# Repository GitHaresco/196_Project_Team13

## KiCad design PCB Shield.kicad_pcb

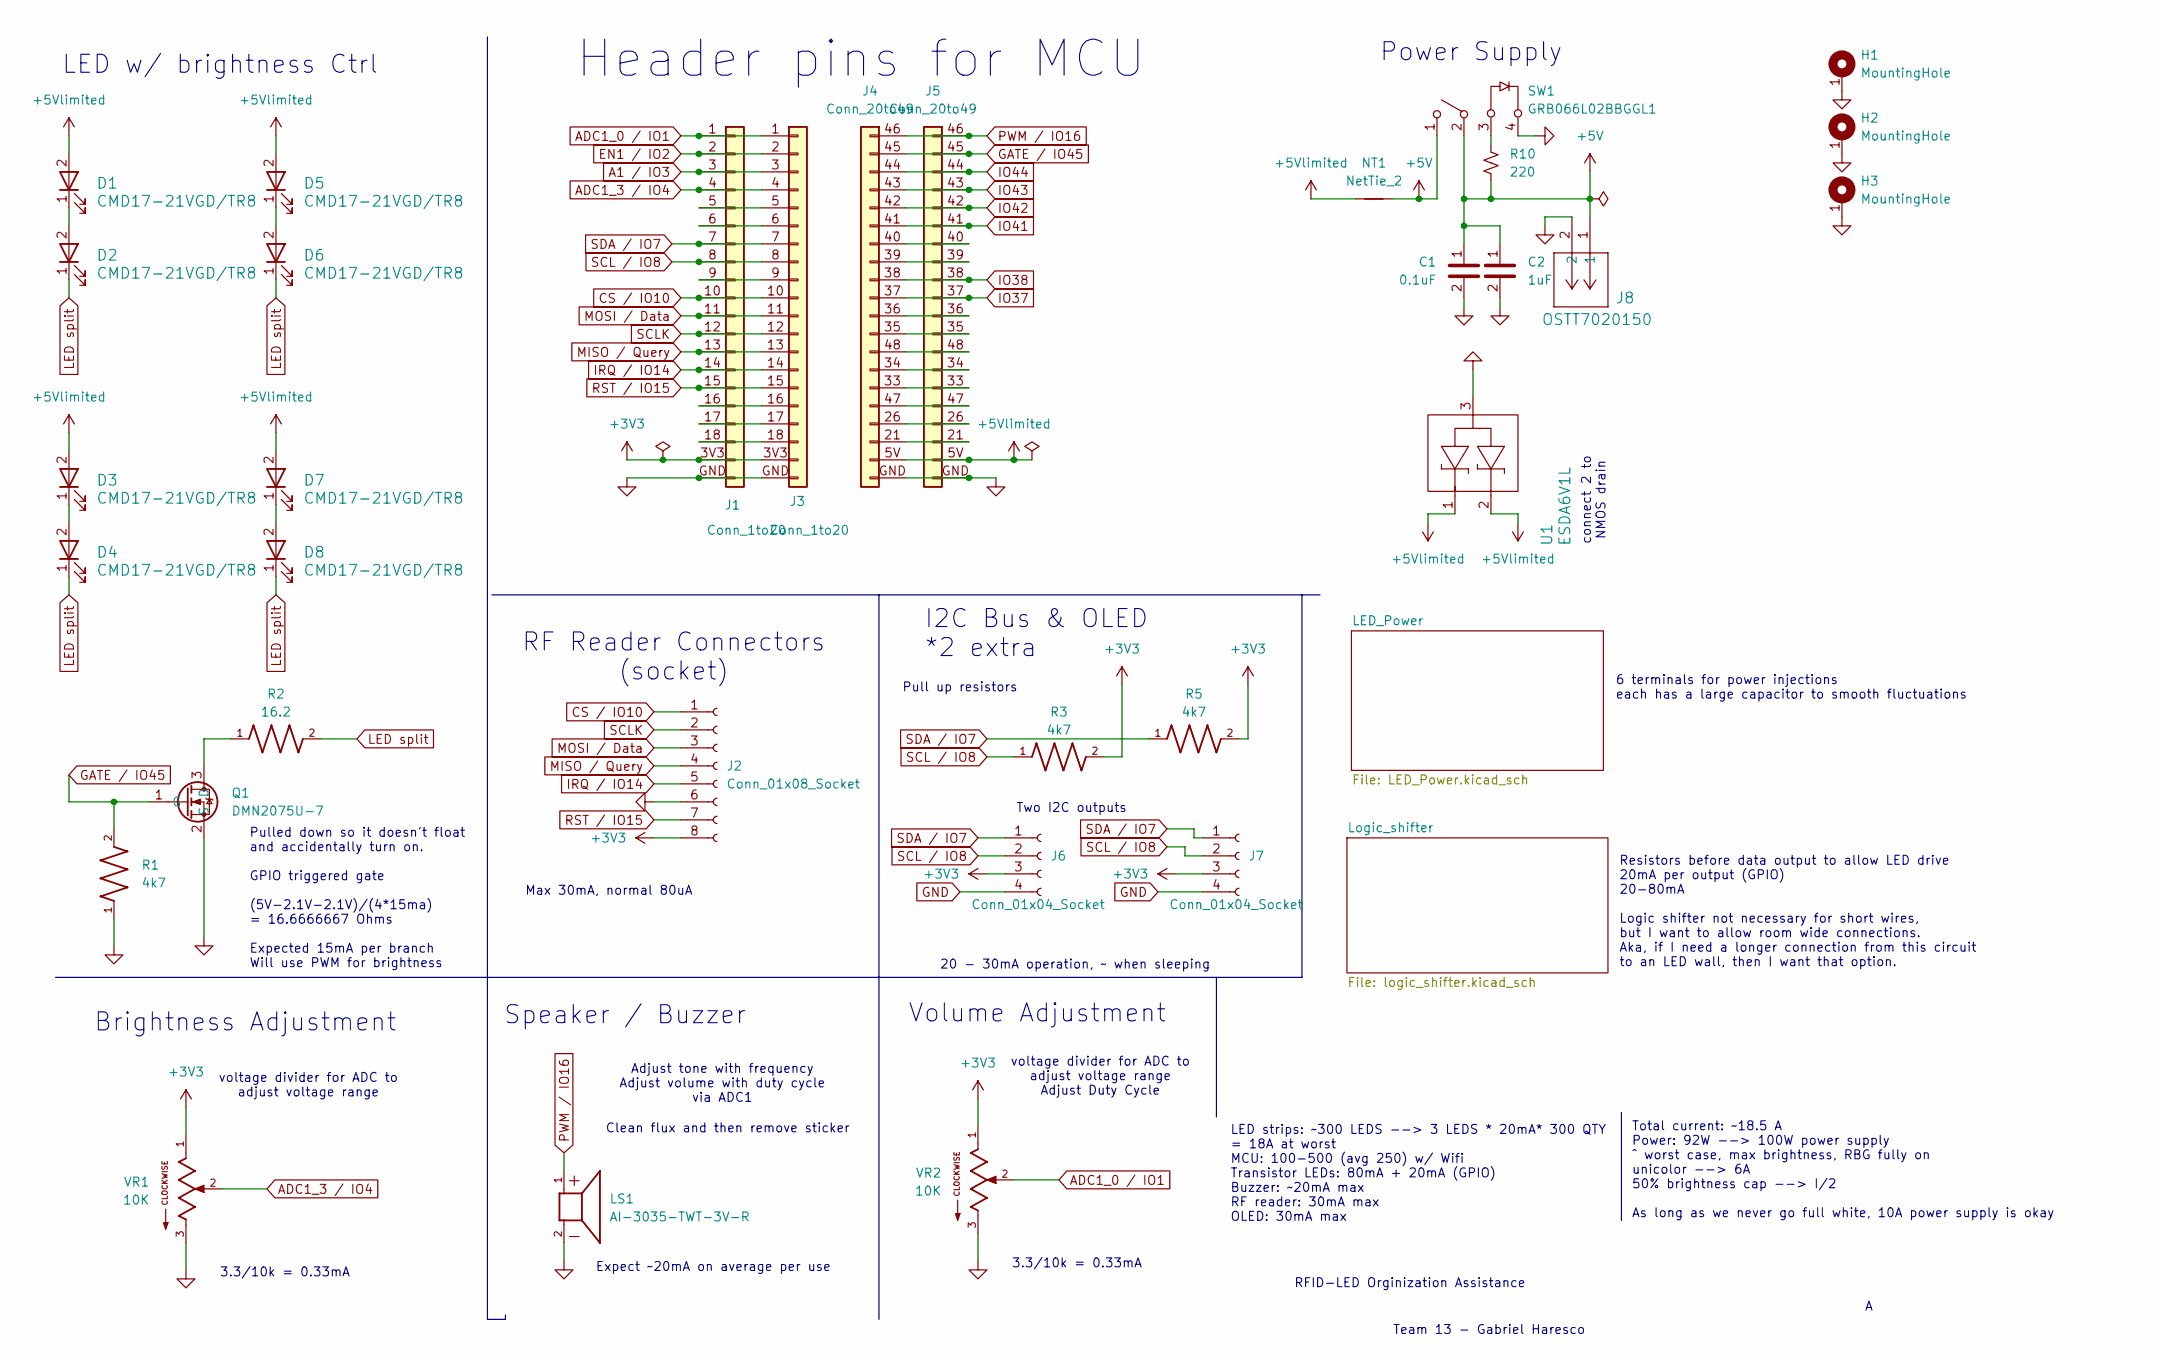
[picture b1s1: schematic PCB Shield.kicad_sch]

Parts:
C1: 0.1uF; CL31B104KBCNNNC; Part Number CL31B104KBCNNNC
C2: 1uF; CL31B105KAHNNNE; Part Number CL31B105KAHNNNE
D1, D2, D3, D4, D5, D6, D7, D8: CMD17-21VGD/TR8; CMD17-21VGD_TR8; Part Number CMD17-21VGD/TR8
H1, H2, H3: MountingHole
J1, J3: Conn_1to20; 196_Conn_1to20; Part Number PH1-20-UA
J2: Conn_01x08_Socket; PinSocket_1x08_P2.54mm_Vertical; Part Number PH1-20-UA
J4, J5: Conn_20to49; 196_Conn_20to48; Part Number PH1-20-UA
J6, J7: Conn_01x04_Socket; PinSocket_1x04_P2.54mm_Vertical; Part Number PH1-20-UA
J8: OSTT7020150; Part Number OSTT7020150
LS1: AI-3035-TWT-3V-R; Buzzer_12x9.5RM7.6; PARTREV E
NT1: NetTie_2; NetTie-2_SMD_Pad2.0mm
Q1: DMN2075U-7; SOT95P237X112-3N-2-V; Part Number DMN2075U-7
R1: 4k7; R_1206_3216Metric; Part Number CRCW120610K0FKEA
R2: 16.2; CRCW120616R2FKEA; Part Number CRCW120616R2FKEA
R3, R5: 4k7; RC1206FR-074K7L; Part Number RC1206FR-074K7L
R10: 220; R_1206_3216Metric; Part Number RCS1206150RJNEA
SW1: GRB066L02BBGGL1; Part Number GRB066L02BBGGL1
U1: ESDA6V1L; SOT_DA6V1L_STM-M; Part Number ESDA6V1L
VR1, VR2: 10K; 3361P-1-103GLF; PARTREV 08/19

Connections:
+3V3: J1.3V3 (Pin_19), J2.8, J3.3V3 (Pin_19), J6.3, J7.3, R3.2, R5.2, VR1.1, VR2.1
+5V: C1.1, C2.1, J8.1, NT1.2, R10.2, SW1.1, SW1.2; also elsewhere on the board
+5Vlimited: D1.2, D3.2, D5.2, D7.2, J4.5V (Pin_19), J5.5V (Pin_19), NT1.1, U1.1, U1.2; also elsewhere on the board
A1 / IO3: J1.3, J3.3; also elsewhere on the board
ADC1_0 / IO1: J1.1, J3.1, VR2.2
ADC1_3 / IO4: J1.4, J3.4, VR1.2
CS / IO10: J1.10, J2.1, J3.10
EN1 / IO2: J1.2, J3.2; also elsewhere on the board
GATE / IO45: J4.45 (Pin_2), J5.45 (Pin_2), Q1.1 (G), R1.2
GND: C1.2, C2.2, H1.1, H2.1, H3.1, J1.GND (Pin_20), J2.6, J3.GND (Pin_20), J4.GND (Pin_20), J5.GND (Pin_20), J6.4, J7.4, J8.2, LS1.2, Q1.2 (S), R1.1, SW1.4, U1.3, VR1.3, VR2.3; also elsewhere on the board
IO37: J4.37 (Pin_10), J5.37 (Pin_10); also elsewhere on the board
IO38: J4.38 (Pin_9), J5.38 (Pin_9); also elsewhere on the board
IO41: J4.41 (42), J5.41 (42); also elsewhere on the board
IO42: J4.42 (Pin_5), J5.42 (Pin_5); also elsewhere on the board
IO43: J4.43 (Pin_4), J5.43 (Pin_4); also elsewhere on the board
IO44: J4.44 (Pin_3), J5.44 (Pin_3); also elsewhere on the board
IRQ / IO14: J1.14, J2.5, J3.14
LED split: D2.1, D4.1, D6.1, D8.1, R2.2
MISO / Query: J1.13, J2.4, J3.13
MOSI / Data: J1.11, J2.3, J3.11
unnamed: D1.1, D2.2
unnamed: D3.1, D4.2
unnamed: D5.1, D6.2
unnamed: D7.1, D8.2
unnamed: J1.5, J3.5
unnamed: J1.6, J3.6
unnamed: J1.9, J3.9
unnamed: J1.16, J3.16
unnamed: J1.17, J3.17
unnamed: J1.18, J3.18
unnamed: J4.40 (Pin_7), J5.40 (Pin_7)
unnamed: J4.39 (Pin_8), J5.39 (Pin_8)
unnamed: J4.36 (Pin_11), J5.36 (Pin_11)
unnamed: J4.35 (Pin_12), J5.35 (Pin_12)
unnamed: J4.48 (Pin_13), J5.48 (Pin_13)
unnamed: J4.34 (Pin_14), J5.34 (Pin_14)
unnamed: J4.33 (Pin_15), J5.33 (Pin_15)
unnamed: J4.47 (Pin_16), J5.47 (Pin_16)
unnamed: J4.26 (Pin_17), J5.26 (Pin_17)
unnamed: J4.21 (Pin_18), J5.21 (Pin_18)
unnamed: Q1.3 (D), R2.1
unnamed: R10.1, SW1.3
PWM / IO16: J4.46 (Pin_1), J5.46 (Pin_1), LS1.1
RST / IO15: J1.15, J2.7, J3.15
SCL / IO8: J1.8, J3.8, J6.2, J7.2, R3.1
SCLK: J1.12, J2.2, J3.12
SDA / IO7: J1.7, J3.7, J6.1, J7.1, R5.1

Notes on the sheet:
voltage divider for ADC to adjust voltage range
Max 30mA, normal 80uA
LED w/ brightness Ctrl
voltage divider for ADC to adjust voltage range Adjust Duty Cycle
Pull up resistors
LED strips: ~300 LEDS --> 3 LEDS * 20mA* 300 QTY = 18A at worst MCU: 100-500 (avg 250) w/ Wifi Transistor LEDs: 80mA + 20mA (GPIO) Buzzer: ~20mA max RF reader: 30mA max OLED: 30mA max
I2C Bus & OLED *2 extra
Resistors before data output to allow LED drive 20mA per output (GPIO) 20-80mA Logic shifter not necessary for short wires, but I want to allow room wide connections. Aka, if I need a longer connection from this circuit to an LED wall, then I want that option.
Brightness Adjustment
Team 13 - Gabriel Haresco
RF Reader Connectors (socket)
Total current: ~18.5 A Power: 92W --> 100W power supply ^ worst case, max brightness, RBG fully on unicolor --> 6A 50% brightness cap --> I/2 As long as we never go full white, 10A power supply is okay
Speaker / Buzzer
Power Supply
RFID-LED Orginization Assistance
Clean flux and then remove sticker
20 - 30mA operation, ~ when sleeping
Adjust tone with frequency Adjust volume with duty cycle via ADC1
3.3/10k = 0.33mA
Volume Adjustment
Pulled down so it doesn't float and accidentally turn on. GPIO triggered gate (5V-2.1V-2.1V)/(4*15ma) = 16.6666667 Ohms Expected 15mA per branch Will use PWM for brightness
Expect ~20mA on average per use
6 terminals for power injections each has a large capacitor to smooth fluctuations
Two I2C outputs
connect 2 to NMOS drain
Header pins for MCU

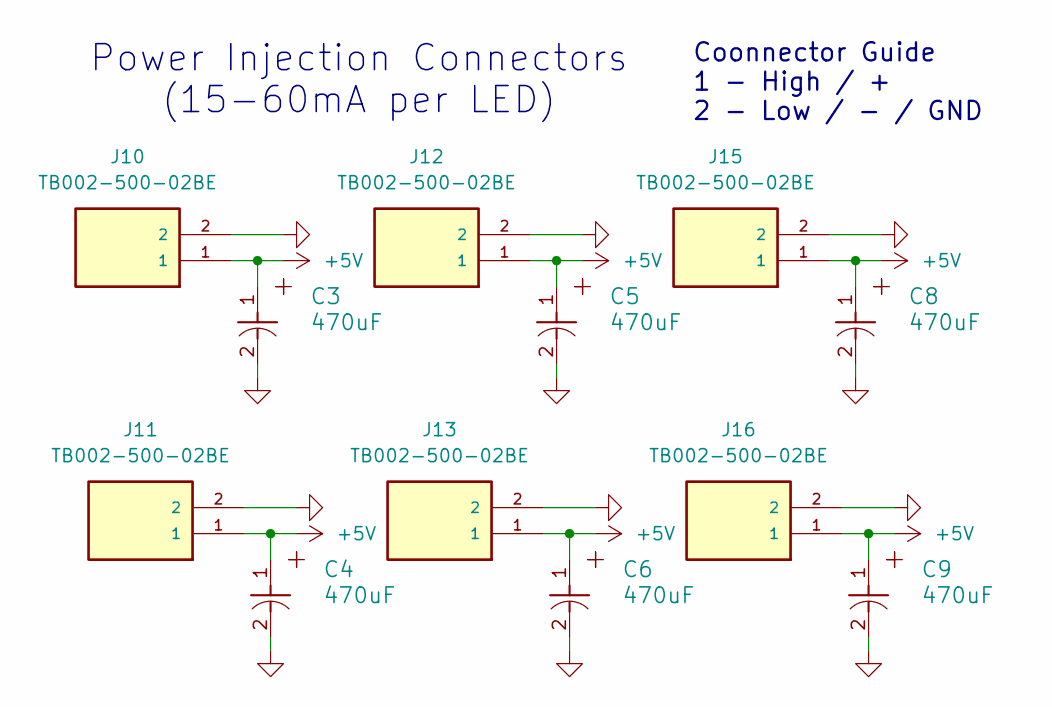
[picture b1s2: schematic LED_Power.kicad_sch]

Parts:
C3, C4, C5, C6, C8, C9: 470uF; 25ZLH470MEFC10X12; Part Number 25ZLH470MEFC10X12.5
J10, J11, J12, J13, J15, J16: TB002-500-02BE; Part Number TB002-500-02BE

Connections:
+5V: C3.1, C4.1, C5.1, C6.1, C8.1, C9.1, J10.1, J11.1, J12.1, J13.1, J15.1, J16.1; also elsewhere on the board
GND: C3.2, C4.2, C5.2, C6.2, C8.2, C9.2, J10.2, J11.2, J12.2, J13.2, J15.2, J16.2; also elsewhere on the board

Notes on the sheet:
Power Injection Connectors (15-60mA per LED)
Coonnector Guide 1 - High / + 2 - Low / - / GND

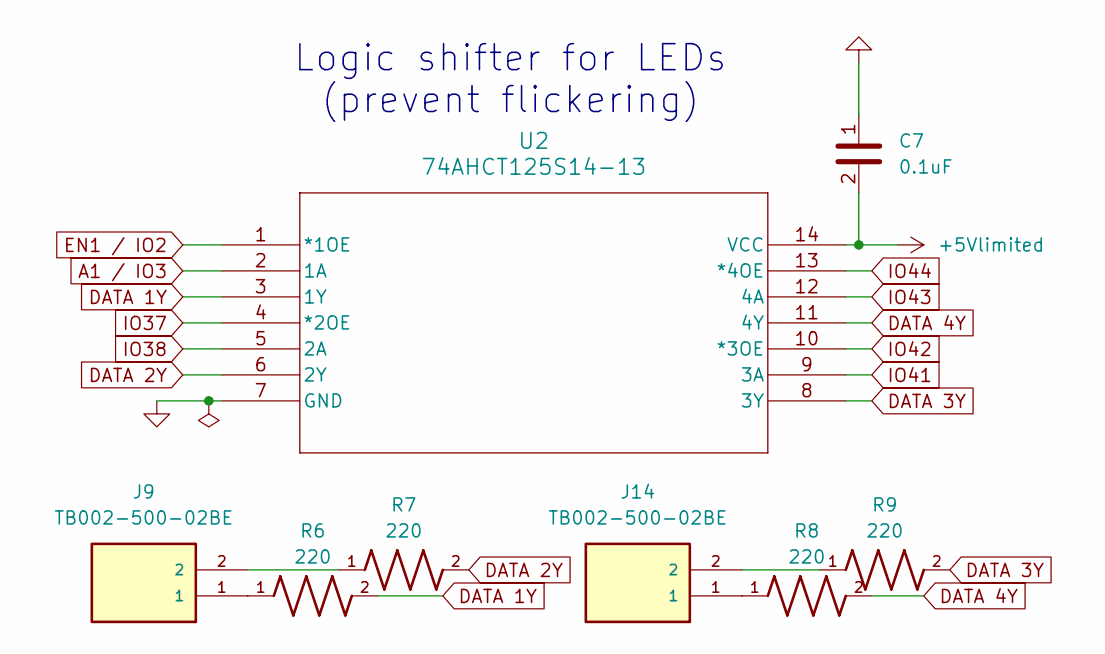
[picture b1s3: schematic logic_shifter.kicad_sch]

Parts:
C7: 0.1uF; CL31B104KBCNNNC; Part Number CL31B104KBCNNNC
J9, J14: TB002-500-02BE; Part Number TB002-500-02BE
R6, R7, R8, R9: 220; RMCF1206FT220R; Part Number RMCF1206FT220R
U2: 74AHCT125S14-13; Part Number 74AHCT125S14-13

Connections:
+5Vlimited: C7.2, U2.14 (VCC); also elsewhere on the board
A1 / IO3: U2.2 (1A); also elsewhere on the board
DATA 1Y: R6.2, U2.3 (1Y)
DATA 2Y: R7.2, U2.6 (2Y)
DATA 3Y: R9.2, U2.8 (3Y)
DATA 4Y: R8.2, U2.11 (4Y)
EN1 / IO2: U2.1 (*1OE); also elsewhere on the board
GND: C7.1, U2.7 (GND); also elsewhere on the board
IO37: U2.4 (*2OE); also elsewhere on the board
IO38: U2.5 (2A); also elsewhere on the board
IO41: U2.9 (3A); also elsewhere on the board
IO42: U2.10 (*3OE); also elsewhere on the board
IO43: U2.12 (4A); also elsewhere on the board
IO44: U2.13 (*4OE); also elsewhere on the board
unnamed: J9.1, R6.1
unnamed: J9.2, R7.1
unnamed: J14.1, R8.1
unnamed: J14.2, R9.1

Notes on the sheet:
Logic shifter for LEDs (prevent flickering)

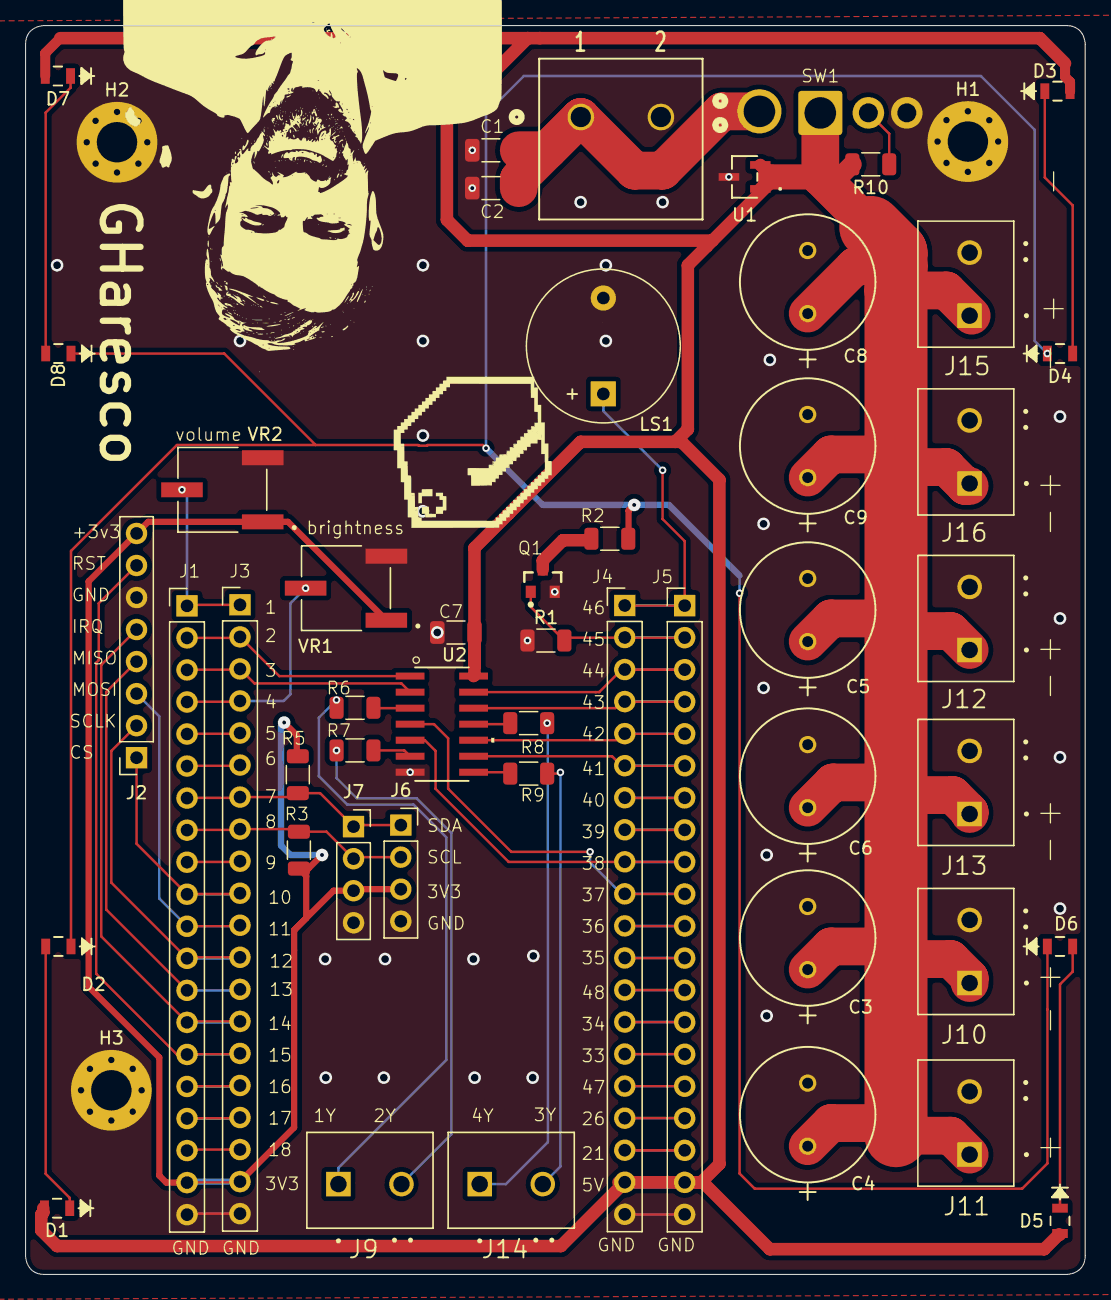
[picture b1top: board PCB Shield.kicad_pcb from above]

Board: 4 copper layers, 84.0 x 99.0 mm, 53 parts (0 on the bottom side), 55 nets.

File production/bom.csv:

Designator,Footprint,Quantity,Value,LCSC Part #
"C1, C7",CL31B104KBCNNNC,2,0.1uF,
C2,CL31B105KAHNNNE,1,1uF,
"C3, C4, C5, C6, C8, C9",25ZLH470MEFC10X12,6,470uF,
"D1, D2, D3, D4, D5, D6, D7, D8",CMD17-21VGD_TR8,8,CMD17-21VGD/TR8,
"J1, J3",196_Conn_1to20,2,Conn_1to20,
"J10, J11, J12, J13, J14, J15, J16, J9",TB002-500-02BE,8,TB002-500-02BE,
J2,PinSocket_1x08_P2.54mm_Vertical,1,Conn_01x08_Socket,
"J4, J5",196_Conn_20to48,2,Conn_20to49,
"J6, J7",PinSocket_1x04_P2.54mm_Vertical,2,Conn_01x04_Socket,
J8,OSTT7020150,1,OSTT7020150,
LS1,Buzzer_12x9.5RM7.6,1,AI-3035-TWT-3V-R,
Q1,SOT95P237X112-3N-2-V,1,DMN2075U-7,
R1,1206,1,4k7,
R10,1206,1,220,
R2,CRCW120616R2FKEA,1,16.2,
"R3, R5",RC1206FR-074K7L,2,4k7,
"R6, R7, R8, R9",RMCF1206FT220R,4,220,
SW1,GRB066L02BBGGL1,1,GRB066L02BBGGL1,
U1,SOT_DA6V1L_STM-M,1,ESDA6V1L,
U2,74AHCT125S14-13,1,74AHCT125S14-13,
"VR1, VR2",3361P-1-103GLF,2,10K,

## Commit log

2026-04-27 Fix git setup, ignore history and temp files
2026-04-27 Clean stable KiCad project state
2026-04-27 finally fix libraries?
2026-04-27 got rid of last annoying old library
2026-04-27 5:30am progress so far
2026-04-27 Finally done?
2026-04-27 Hopefully this works
2026-04-28 4/27 work today
2026-04-29 gave all footprints proper names and descriptions
2026-04-29 edited 4 schematic symbols
2026-04-29 made sure footprints saved, and they did
2026-04-29 finished component symbols, mostly
2026-04-29 added transistor to libraries
2026-04-29 added switch
2026-04-29 all shematic changes made
2026-04-29 figured out how to remap symbols on schematic quickly and did so
2026-04-29 Fixed all components and updated parts
2026-04-29 put components on PCB and added outline
2026-04-29 final saves
2026-04-29 placed PCB components somewhat how I want it
2026-04-29 routing almost done
2026-04-30 routing progress + planning
2026-04-30 most of routing finished
2026-04-30 finished routing and now just need to check 3d models
2026-04-30 updated header pins
2026-04-30 FINISHED
2026-04-30 finished finally finally
2026-04-30 made shopping list
2026-04-30 swapped out out of stock / weird order components
2026-04-30 quick
2026-04-30 finally done ????
2026-04-30 changed switch
2026-04-30 finished finally and totally. parts ready to order too.
2026-04-30 saving myself
2026-04-30 saved by the bell
2026-04-30 edited and ready
2026-04-30 STILL need to adjust to 30.5mm
2026-05-01 finally order ready
2026-05-01 submitted
2026-05-03 last minute changes
2026-05-16 hopefully it pushes. Flipped the headers and shrunk down board
2026-05-16 fixed everything
